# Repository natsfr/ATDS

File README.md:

# ATDS
Amateur Tracking and Data System
Abandonned project because OnSemi retired their AX transceivers without notices !

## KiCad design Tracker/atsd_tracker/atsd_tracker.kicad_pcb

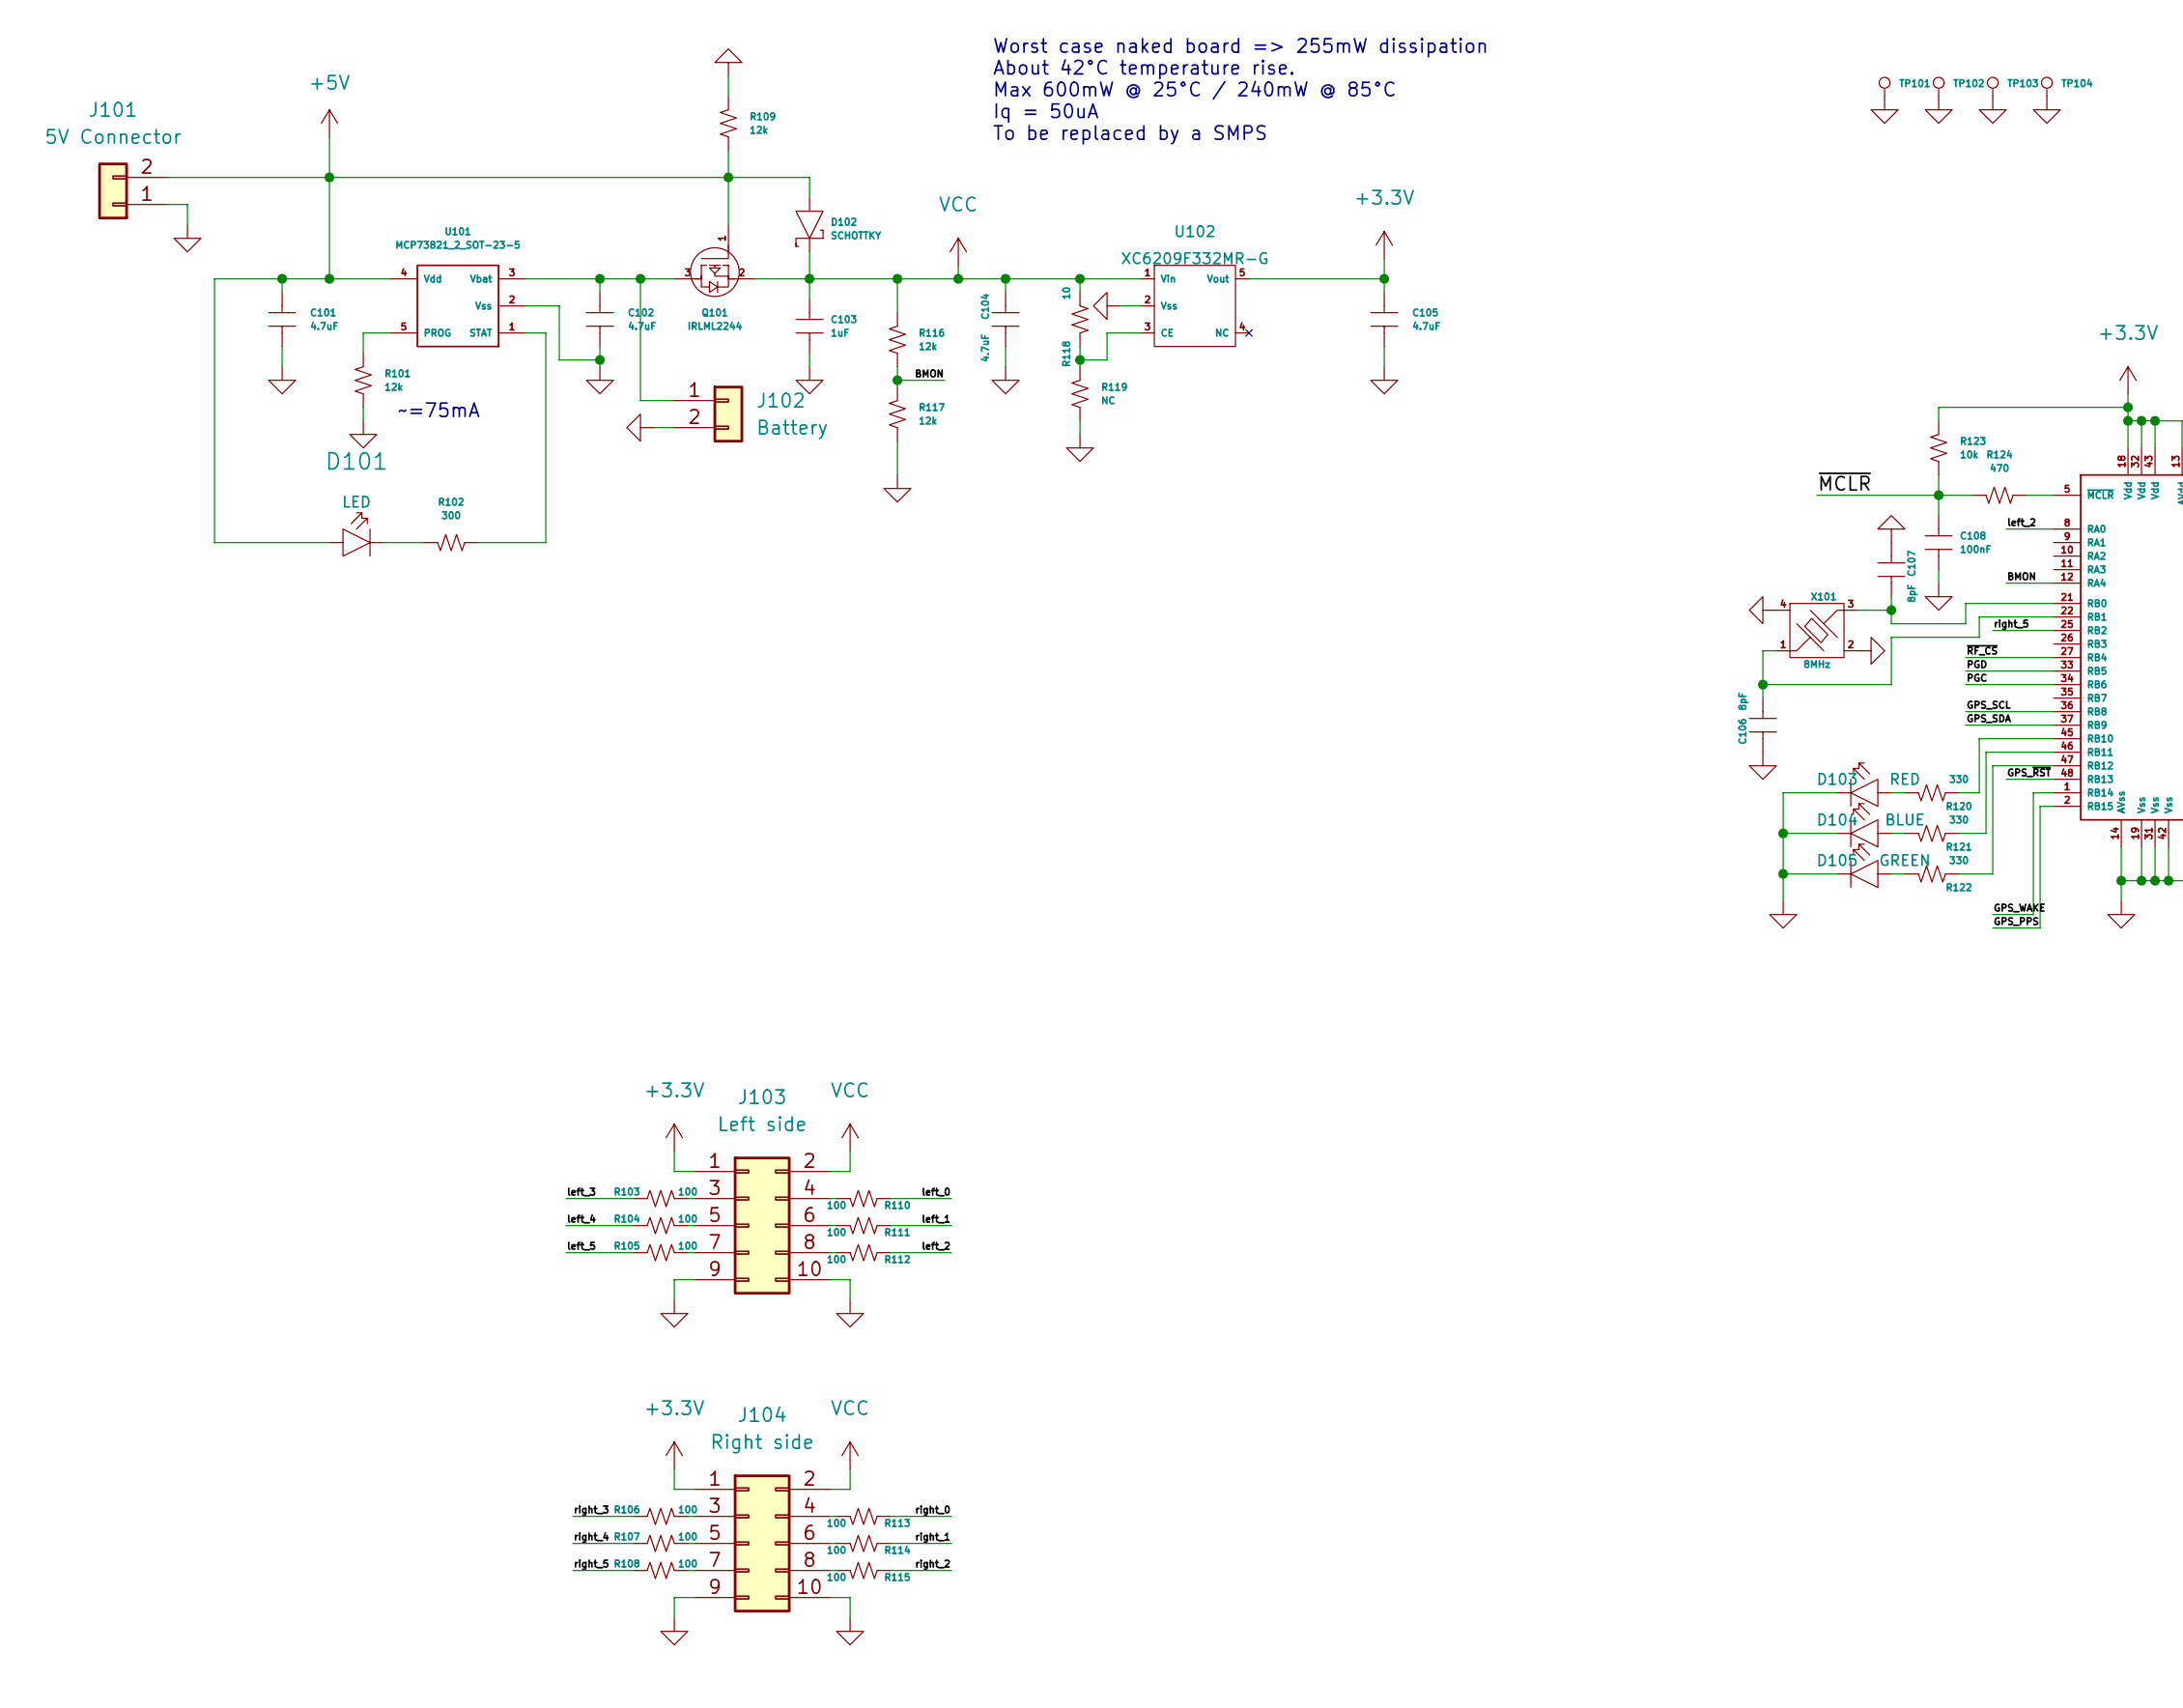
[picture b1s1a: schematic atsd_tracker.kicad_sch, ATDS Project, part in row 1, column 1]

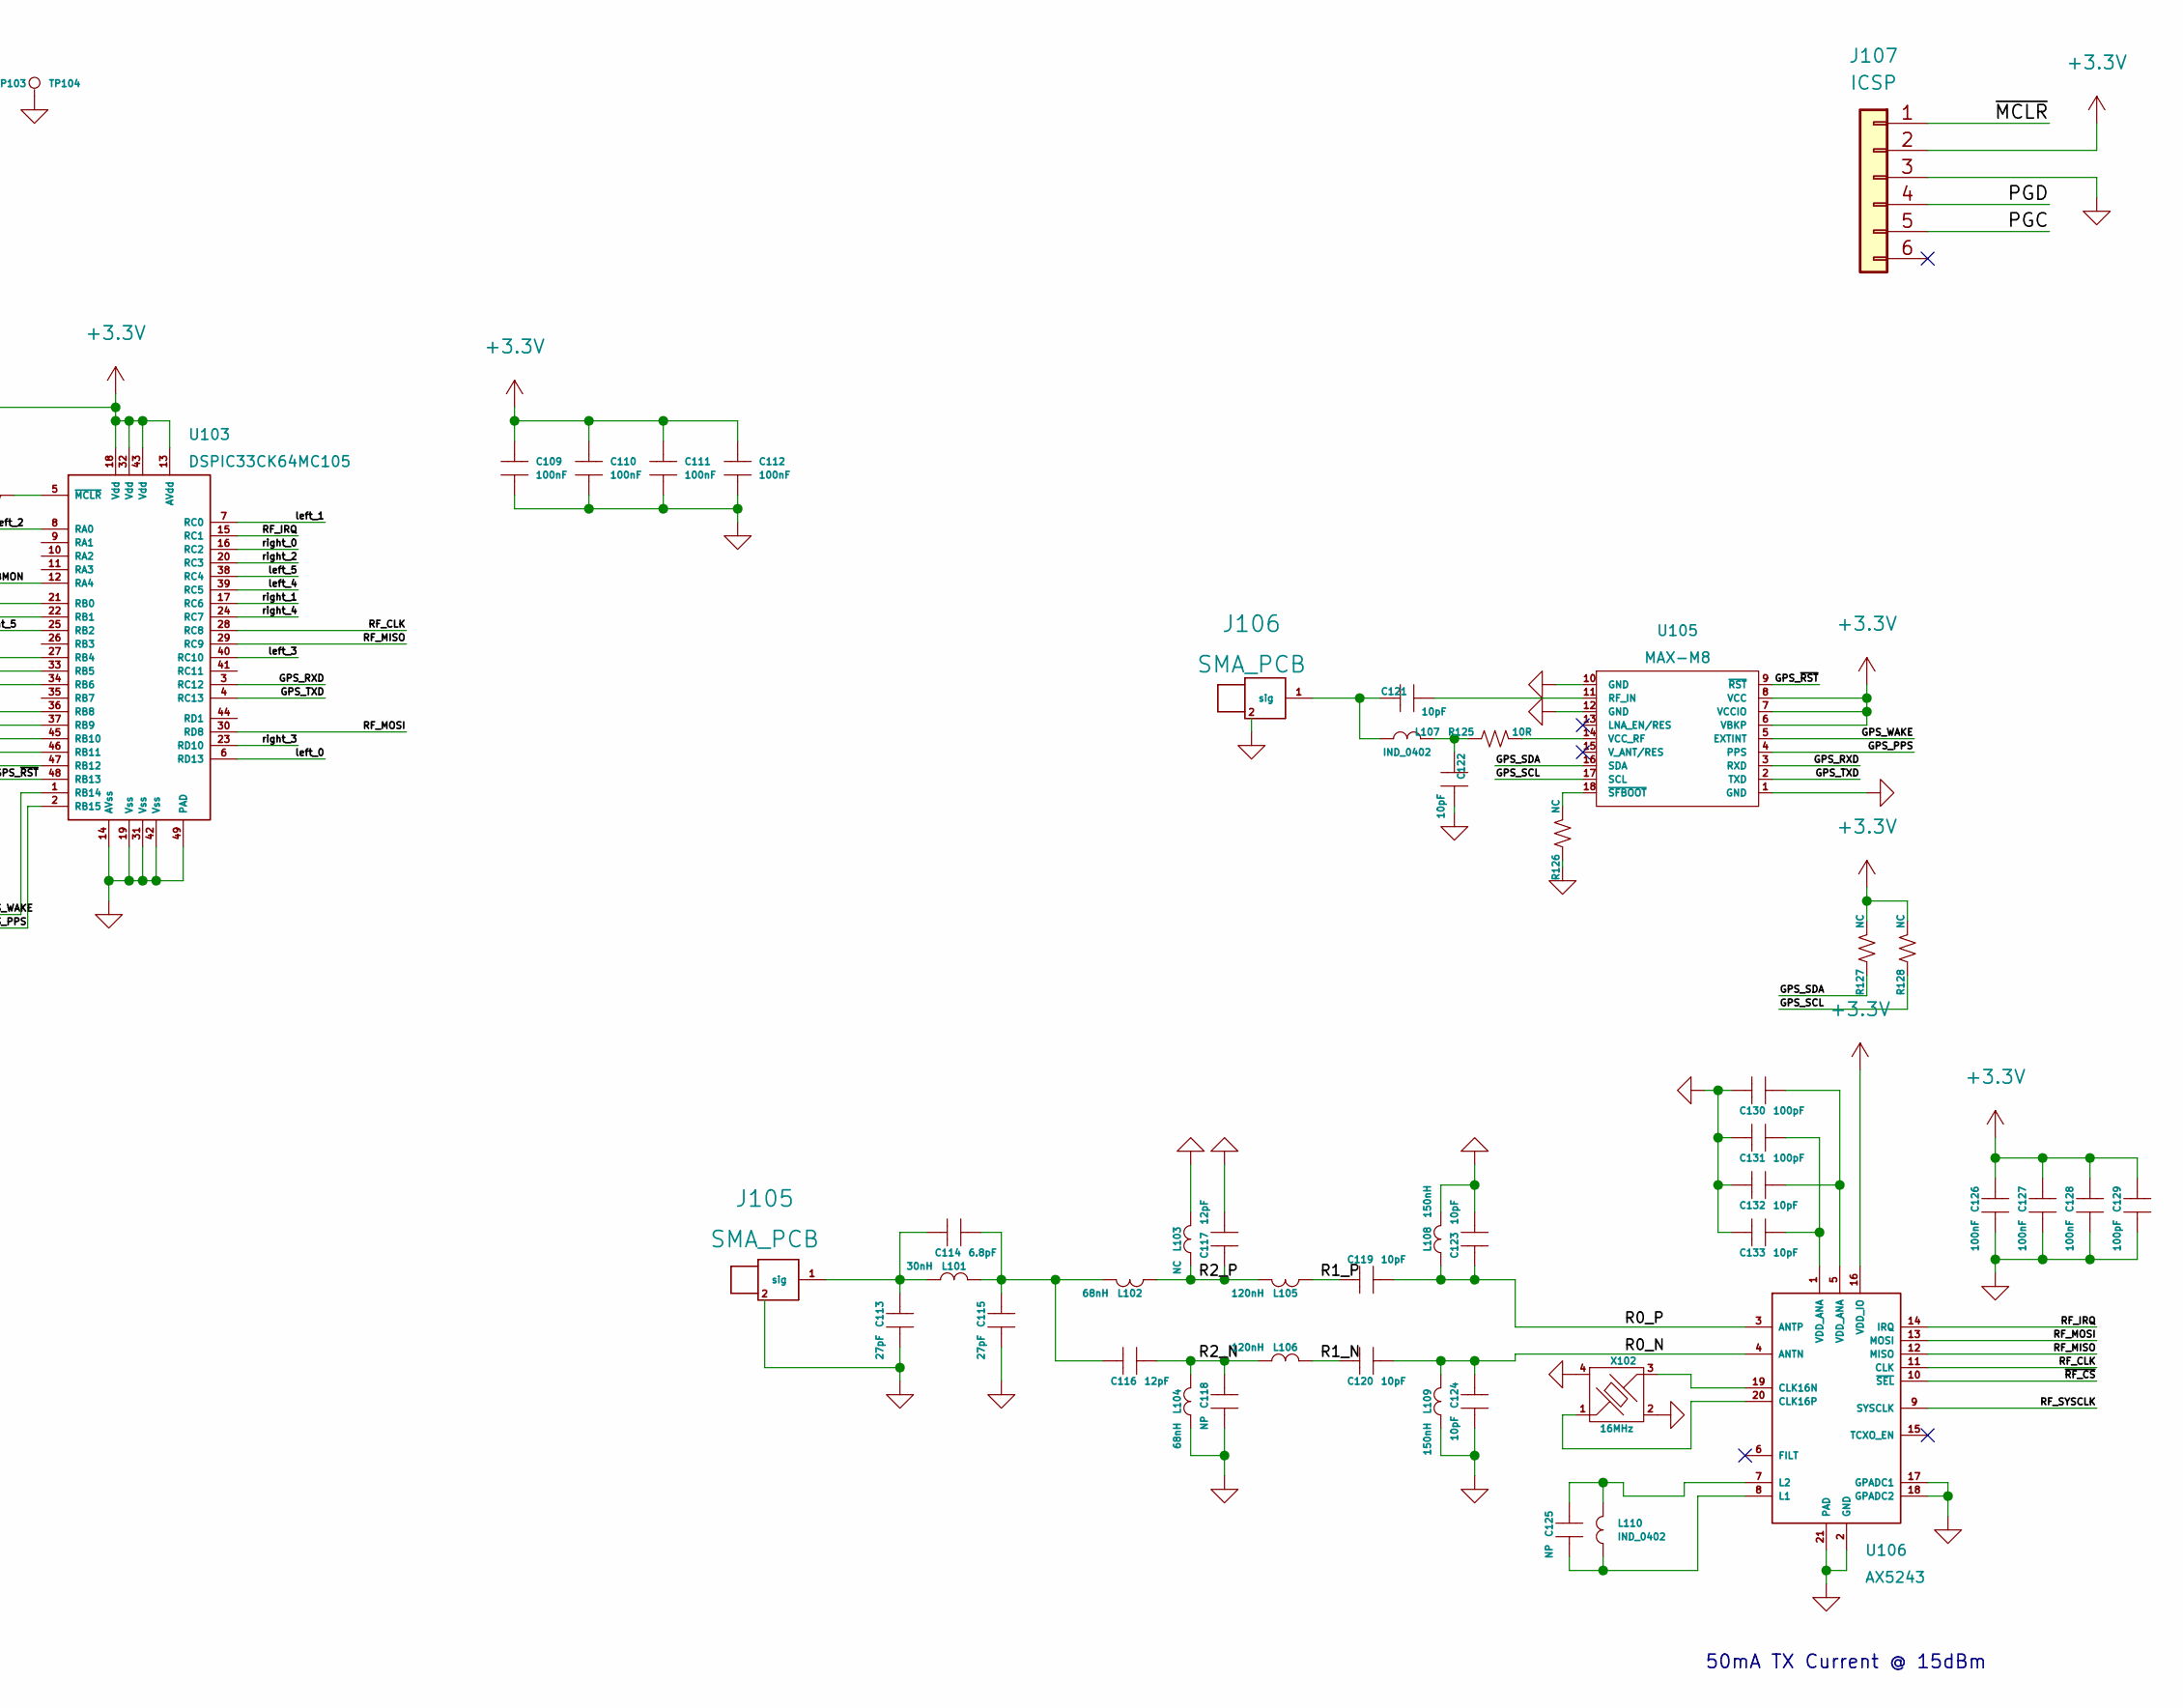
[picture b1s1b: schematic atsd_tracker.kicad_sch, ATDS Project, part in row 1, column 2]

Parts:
C101, C102, C104, C105: 4.7uF; SM0805
C103: 1uF; SM0603
C106, C107: 8pF; SM0402
C108, C109, C110, C111, C112, C126, C127, C128: 100nF; SM0402
C113, C115: 27pF; SM0402
C114: 6.8pF; SM0402
C116, C117: 12pF; SM0402
C118, C125: NP; SM0402
C119, C120, C121, C122, C123, C124, C132, C133: 10pF; SM0402
C129, C130, C131: 100pF; SM0402
D101: LED; LED-0603
D102: SCHOTTKY; SOD-123
D103: RED; LED-0603
D104: BLUE; LED-0603
D105: GREEN; LED-0603
J101: 5V Connector; JST_XH_B2B-XH-A_1x02_P2.50mm_Vertical
J102: Battery; JST_XH_B2B-XH-A_1x02_P2.50mm_Vertical
J103: Left side; PinHeader_2x05_P1.27mm_Vertical
J104: Right side; PinHeader_2x05_P1.27mm_Vertical
J105, J106: SMA_PCB; SMA_RA_PCB_Amphenol
J107: ICSP; PinHeader_1x06_P2.54mm_Vertical
L101: 30nH; SM0402
L102, L104: 68nH; SM0402
L103: NC; SM0402
L105, L106: 120nH; SM0402
L107, L110: IND_0402; SM0402
L108, L109: 150nH; SM0402
Q101: IRLML2244; SOT-23
R101, R109, R116, R117: 12k; SM0603
R102: 300; SM0603
R103, R104, R105, R106, R107, R108, R110, R111, R112, R113, R114, R115: 100; SM0402
R118: 10; SM0402
R119, R126, R127, R128: NC; SM0402
R120, R121, R122: 330; SM0402
R123: 10k; SM0402
R124: 470; SM0402
R125: 10R; SM0402
TP101, TP102, TP103, TP104: TP1; 3.1mm_Plated
U101: MCP73821_2_SOT-23-5; SOT23-5
U102: XC6209F332MR-G; SOT25-5
U103: DSPIC33CK64MC105; DSPIC33_QFN48_UTPQF_6x6_0.4mm
U105: MAX-M8
U106: AX5243; AX5243_QFN-5x5_EP_4x4_Pitch0.5mm
X101: 8MHz; xtal_3.2x2.5
X102: 16MHz; xtal_3.2x2.5

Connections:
+3V3: C105.2, C109.2, C110.2, C111.2, C112.2, C126.2, C127.2, C128.2, C129.2, J103.1, J104.1, J107.2, R123.2, R127.2, R128.2, U102.5 (Vout), U103.13 (AVdd), U103.18 (Vdd), U103.32 (Vdd), U103.43 (Vdd), U105.6 (VBKP), U105.7 (VCCIO), U105.8 (VCC), U106.16 (VDD_IO)
+5V: C101.2, D101.A, D102.A, J101.2, Q101.1 (G), R109.1, U101.4 (Vdd)
/BMON: R116.1, R117.2, U103.12 (RA4)
/GPS_PPS: U103.2 (RB15), U105.4 (PPS)
/GPS_RXD: U103.3 (RC12), U105.3 (RXD)
/GPS_SCL: R128.1, U103.36 (RB8), U105.17 (SCL)
/GPS_SDA: R127.1, U103.37 (RB9), U105.16 (SDA)
/GPS_TXD: U103.4 (RC13), U105.2 (TXD)
/GPS_WAKE: U103.1 (RB14), U105.5 (EXTINT)
/GPS_~RST: U103.48 (RB13), U105.9 (~RST)
/PGC: J107.5, U103.34 (RB6)
/PGD: J107.4, U103.33 (RB5)
/R0_N: C120.1, C124.2, L109.2, U106.4 (ANTN)
/R0_P: C119.1, C123.2, L108.2, U106.3 (ANTP); also elsewhere on the board
/R1_N: C120.2, L106.2
/R1_P: C119.2, L105.2
/R2_N: C116.1, C118.2, L104.2, L106.1
/R2_P: C117.2, L102.2, L103.1, L105.1
/RF_CLK: U103.28 (RC8), U106.11 (CLK)
/RF_IRQ: U103.15 (RC1), U106.14 (IRQ)
/RF_MISO: U103.29 (RC9), U106.12 (MISO)
/RF_MOSI: U103.30 (RD8), U106.13 (MOSI)
/RF_SYSCLK: U106.9 (SYSCLK)
/left_0: R110.1, U103.6 (RD13)
/left_1: R111.1, U103.7 (RC0)
/left_2: R112.1, U103.8 (RA0)
/left_3: R103.1, U103.40 (RC10)
/left_4: R104.1, U103.39 (RC5)
/left_5: R105.1, U103.38 (RC4)
/right_0: R113.1, U103.16 (RC2)
/right_1: R114.1, U103.17 (RC6)
/right_2: R115.1, U103.20 (RC3)
/right_3: R106.1, U103.23 (RD10)
/right_4: R107.1, U103.24 (RC7)
/right_5: R108.1, U103.25 (RB2)
/~MCLR: C108.2, J107.1, R123.1, R124.2
/~RF_CS: U103.27 (RB4), U106.10 (~SEL)
GND: C101.1, C102.1, C103.1, C104.1, C105.1, C106.2, C107.2, C108.1, C109.1, C110.1, C111.1, C112.1, C113.1, C115.1, C117.1, C118.1, C122.1, C123.1, C124.1, C126.1, C127.1, C128.1, C129.1, C130.2, C131.2, C132.2, C133.2, D103.K, D104.K, D105.K, J101.1, J102.2, J103.9, J103.10, J104.9, J104.10, J105.2, J106.2, J107.3, L103.2, L104.1, L108.1, L109.1, R101.1, R109.2, R117.1, R119.1, R126.1, TP101.1, TP102.1, TP103.1, TP104.1, U101.2 (Vss), U102.2 (Vss), U103.14 (AVss), U103.19 (Vss), U103.31 (Vss), U103.42 (Vss), U103.49 (PAD), U105.1 (GND), U105.10 (GND), U105.12 (GND), U106.2 (GND), U106.17 (GPADC1), U106.18 (GPADC2), U106.21 (PAD), X101.2, X101.4, X102.2, X102.4; also elsewhere on the board
unnamed: C102.2, J102.1, Q101.3 (D), U101.3 (Vbat)
unnamed: C106.1, U103.22 (RB1), X101.1
unnamed: C107.1, U103.21 (RB0), X101.3
unnamed: C113.2, C114.2, J105.1 (sig), L101.1
unnamed: C114.1, C115.2, C116.2, L101.2, L102.1
unnamed: C121.1, U105.11 (RF_IN)
unnamed: C121.2, J106.1 (sig), L107.1
unnamed: C122.2, L107.2, R125.1
unnamed: C125.1, L110.1, U106.8 (L1)
unnamed: C125.2, L110.2, U106.7 (L2)
unnamed: D101.K, R102.2
unnamed: D103.A, R120.2
unnamed: D104.A, R121.2
unnamed: D105.A, R122.2
unnamed: J103.3, R103.2
unnamed: J103.4, R110.2
unnamed: J103.5, R104.2
unnamed: J103.6, R111.2
unnamed: J103.7, R105.2
unnamed: J103.8, R112.2
unnamed: J104.3, R106.2
unnamed: J104.4, R113.2
unnamed: J104.5, R107.2
unnamed: J104.6, R114.2
unnamed: J104.7, R108.2
unnamed: J104.8, R115.2
unnamed: R101.2, U101.5 (PROG)
unnamed: R102.1, U101.1 (STAT)
unnamed: R118.2, R119.2, U102.3 (CE)
unnamed: R120.1, U103.45 (RB10)
unnamed: R121.1, U103.46 (RB11)
unnamed: R122.1, U103.47 (RB12)
unnamed: R124.1, U103.5 (~MCLR)
unnamed: R125.2, U105.14 (VCC_RF)
unnamed: R126.2, U105.18 (~SFBOOT)
unnamed: C131.1, C133.1, U106.1 (VDD_ANA)
unnamed: C130.1, C132.1, U106.5 (VDD_ANA)
unnamed: U106.19 (CLK16N), X102.3
unnamed: U106.20 (CLK16P), X102.1
VCC: C103.2, C104.2, D102.K, J103.2, J104.2, Q101.2 (S), R116.2, R118.1, U102.1 (Vin)

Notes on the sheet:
Worst case naked board => 255mW dissipation About 42°C temperature rise. Max 600mW @ 25°C / 240mW @ 85°C Iq = 50uA To be replaced by a SMPS
~=75mA
50mA TX Current @ 15dBm

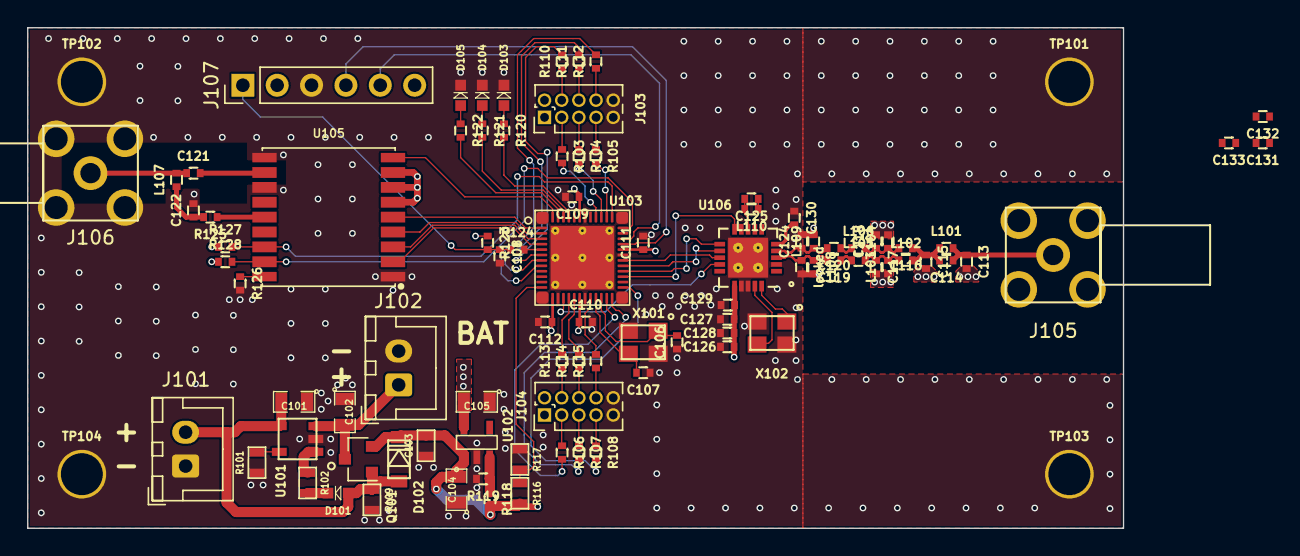
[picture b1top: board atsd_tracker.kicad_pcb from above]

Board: 4 copper layers, 81.0 x 37.0 mm, 95 parts (0 on the bottom side), 77 nets.

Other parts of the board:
locked: 10pF; SM0402

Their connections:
/R0_P: locked.2; also elsewhere on the board
GND: locked.1; also elsewhere on the board

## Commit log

2022-07-30 starting schematic
2022-08-13 Schematic done starting layout
2022-08-24 Produced prototype
2023-02-12 OnSemi discontinued AX5043 and all sub-ghz, switching to si446x

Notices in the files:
Tracker/atsd_tracker/atsd_tracker.kicad_pcb:
F4IHX - CC-BY-SA
